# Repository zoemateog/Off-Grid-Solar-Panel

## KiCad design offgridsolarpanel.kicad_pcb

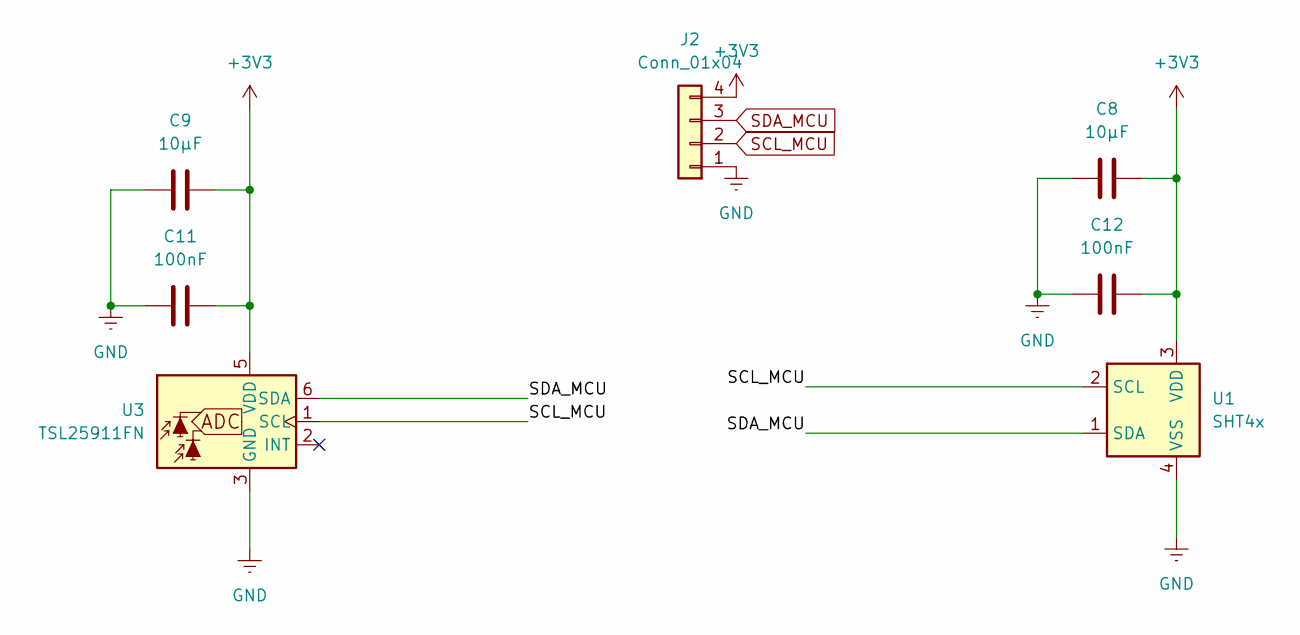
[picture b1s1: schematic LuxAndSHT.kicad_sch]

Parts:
C8, C9: 10μF; C_0805_2012Metric_Pad1.18x1.45mm_HandSolder
C11, C12: 100nF; C_0805_2012Metric_Pad1.18x1.45mm_HandSolder
J2: Conn_01x04; PinHeader_1x04_P1.27mm_Horizontal
U1: SHT4x; Sensirion_DFN-4_1.5x1.5mm_P0.8mm_SHT4x_NoCentralPad
U3: TSL25911FN; AMS_TSL25911FN

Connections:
+3V3: C8.1, C9.2, C11.1, C12.1, J2.4, U1.3 (VDD), U3.5 (VDD); also elsewhere on the board
GND: C8.2, C9.1, C11.2, C12.2, J2.1, U1.4 (VSS), U3.3 (GND); also elsewhere on the board
SCL_MCU: J2.2, U1.2 (SCL), U3.1 (SCL); also elsewhere on the board
SDA_MCU: J2.3, U1.1 (SDA), U3.6 (SDA); also elsewhere on the board

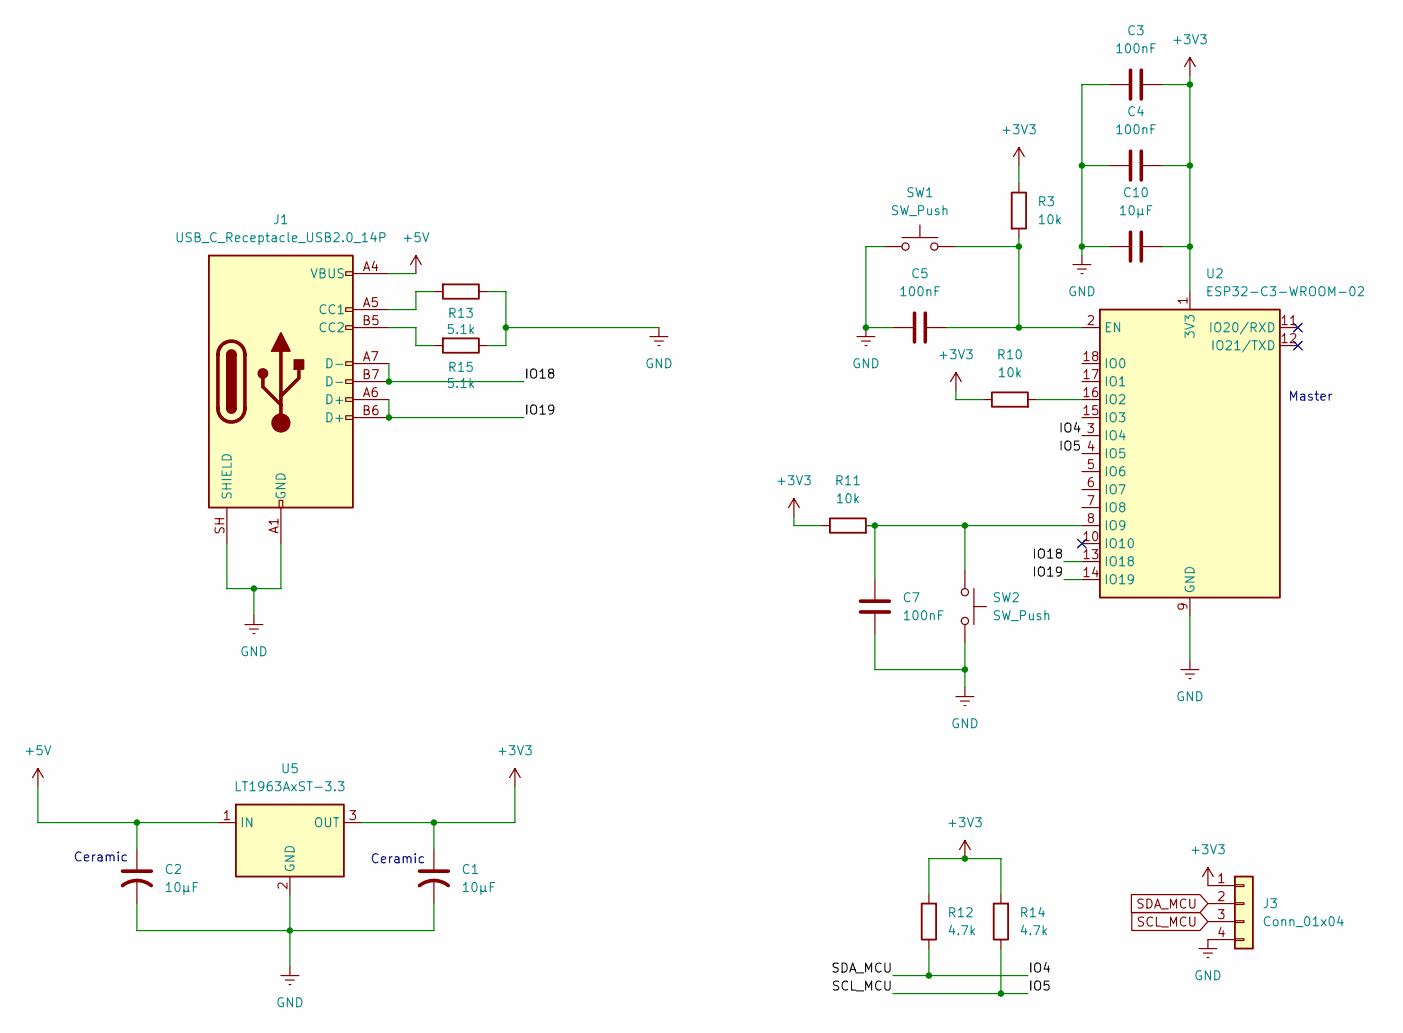
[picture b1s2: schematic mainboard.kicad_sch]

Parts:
C1, C2, C10: 10μF; C_0805_2012Metric_Pad1.18x1.45mm_HandSolder
C3, C4, C5, C7: 100nF; C_0805_2012Metric_Pad1.18x1.45mm_HandSolder
J1: USB_C_Receptacle_USB2.0_14P
J3: Conn_01x04; PinHeader_1x04_P1.27mm_Horizontal
R3, R10, R11: 10k; R_0805_2012Metric_Pad1.20x1.40mm_HandSolder
R12, R14: 4.7k; R_0805_2012Metric_Pad1.20x1.40mm_HandSolder
R13, R15: 5.1k; R_0805_2012Metric_Pad1.20x1.40mm_HandSolder
SW1, SW2: SW_Push; SW_Push_SPST_NO_Alps_SKRK
U2: ESP32-C3-WROOM-02
U5: LT1963AxST-3.3; SOT-223-3_TabPin2

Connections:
+3V3: C1.1, C3.2, C4.2, C10.2, J3.1, R3.1, R10.1, R11.1, R12.2, R14.2, U2.1 (3V3), U5.3 (OUT); also elsewhere on the board
+5V: C2.1, J1.A4 (VBUS), J1.A9 (VBUS), J1.B4 (VBUS), J1.B9 (VBUS), U5.1 (IN)
/Main board/IO18: J1.A7 (D-), J1.B7 (D-), U2.13 (IO18)
/Main board/IO19: J1.A6 (D+), J1.B6 (D+), U2.14 (IO19)
GND: C1.2, C2.2, C3.1, C4.1, C5.1, C7.2, C10.1, J1.A1 (GND), J1.A12 (GND), J1.B1 (GND), J1.B12 (GND), J1.SH (SHIELD), J3.4, R13.1, R15.1, SW1.1, SW2.2, U2.9 (GND), U2.19 (GND), U5.2 (GND); also elsewhere on the board
unnamed: J1.A5 (CC1), R13.2
unnamed: J1.B5 (CC2), R15.2
unnamed: C5.2, R3.2, SW1.2, U2.2 (EN)
unnamed: R10.2, U2.16 (IO2)
unnamed: C7.1, R11.2, SW2.1, U2.8 (IO9)
SCL_MCU: J3.3, R14.1, U2.4 (IO5); also elsewhere on the board
SDA_MCU: J3.2, R12.1, U2.3 (IO4); also elsewhere on the board

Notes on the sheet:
Ceramic
Master

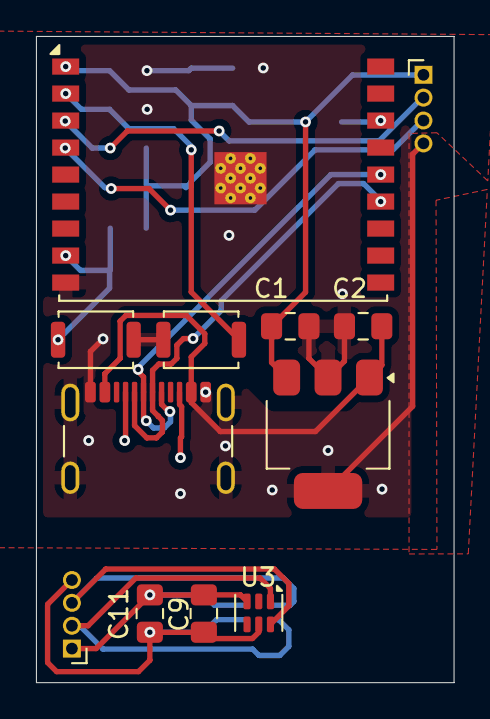
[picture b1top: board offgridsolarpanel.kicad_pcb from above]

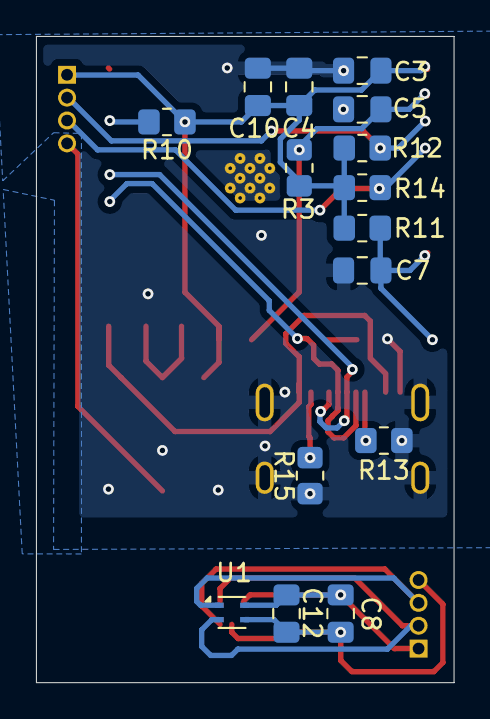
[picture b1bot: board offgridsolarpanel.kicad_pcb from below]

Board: 2 copper layers, 23.2 x 35.9 mm, 27 parts (15 on the bottom side), 12 nets.
